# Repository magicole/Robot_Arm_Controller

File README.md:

# Simple Robot Arm Controller
A project for the control of a simple robotic arm with an Arduino. 

This project is based  around control of a MeArm robotic arm with an Arduino Uno. 
It is separated into two main components, hardware and software. 

## Hardware Overview
This project includes an Arduino shield that is capable of controlling 
all 4 degrees of freedom the MeArm has. It also has the capability
to read potentiometer values for use with a "training" mode. Input 
buttons, status LEDs, and a voltage regulator circuit will also be
placed on the board.

## Software Overview
The software for this project is designed either to run standalone
on the arduino or in conjunction with companion software on a PC.
Software features include a training mode, inverse kinematics, and
serial control. Training mode utilizes a model of the arm with 
potentiometers in place of servo's. This model is manipulated and the arm
mirrors the motions.

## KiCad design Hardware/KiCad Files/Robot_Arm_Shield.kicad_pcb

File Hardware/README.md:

#Hardware

##KiCad Libraries
I used the freetronics KiCad libraries in order to give me a good schematic
symbol and footprint for the Arduino shield. Their GitHub repo can be found here:
https://github.com/freetronics/freetronics_kicad_library
I followed the easy way to install them and the library files are found in the
resources folder of this directory.

## Power Regulator: 
http://www.digikey.com/product-detail/en/stmicroelectronics/L7805CDT-TR/497-7255-1-ND/1884014

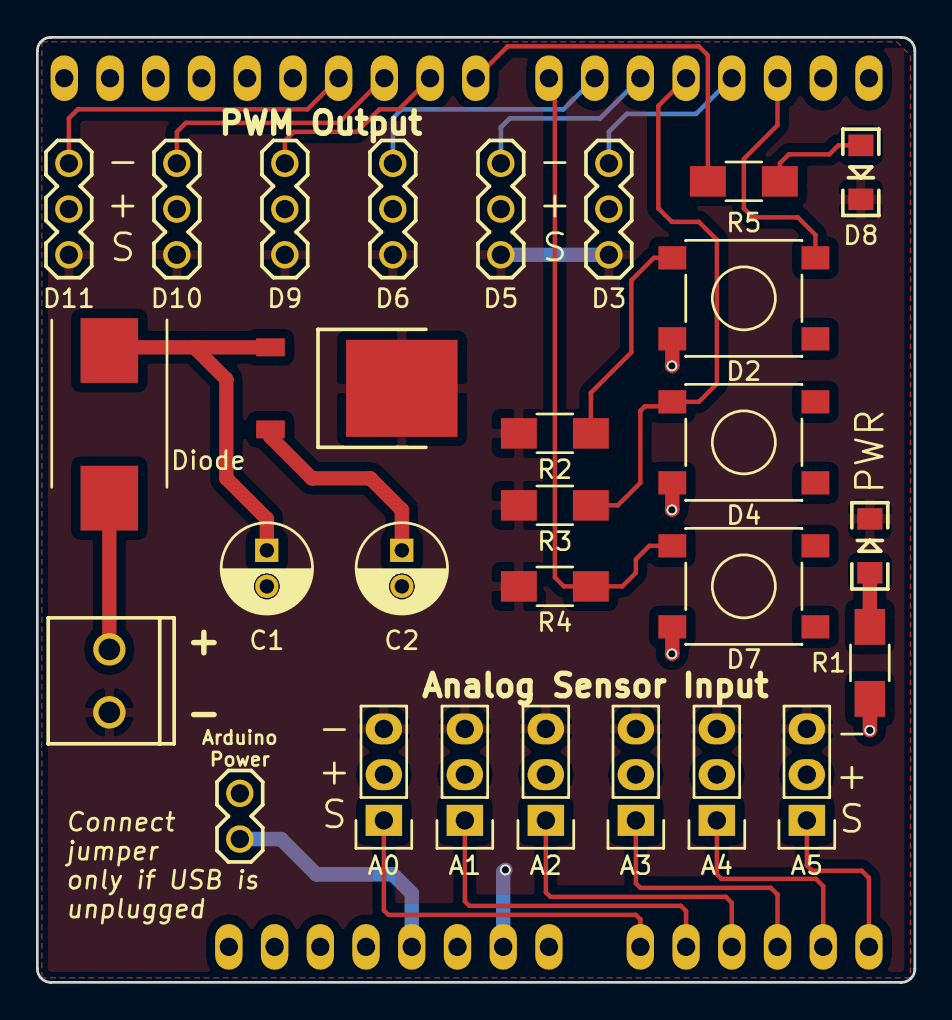
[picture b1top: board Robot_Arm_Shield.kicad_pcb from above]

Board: 2 copper layers, 48.8 x 52.5 mm, 29 parts (0 on the bottom side), 23 nets.

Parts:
A0: Analog In 0; Socket_Strip_Straight_1x03
A1: Analog In 1; Socket_Strip_Straight_1x03
A2: Analog In 2; Socket_Strip_Straight_1x03
A3: Analog In 3; Socket_Strip_Straight_1x03
A4: Analog In 4; Socket_Strip_Straight_1x03
A5: Analog In 5; Socket_Strip_Straight_1x03
C1: 0.33 uF; C_Radial_D5_L11_P2
C2: 0.1 uF; C_Radial_D5_L11_P2
D2: Button 0; SW_SPST_PTS645
D3: Motor 0; 1X03
D4: Button 1; SW_SPST_PTS645
D5: Motor 1; 1X03
D6: Motor 2; 1X03
D7: Button 2; SW_SPST_PTS645
D9: Motor 3; 1X03
D10: Motor 4; 1X03
D11: Motor 5; 1X03
Diode: D_Schottky; DO-214AB_Handsoldering
LED1: Power LED; LED-1206
LED2: Status LED; LED-1206
P1: Power Input; SCREWTERMINAL-3.5MM-2
P14: Power Jumper; 1X02
R1, R5: 150; R_1206_HandSoldering
R2, R3, R4: 10k; R_1206_HandSoldering
SHIELD1: ARDUINO_SHIELD
U1: LM 7805; DPAK

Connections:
/5V: A0.2, A1.2, A2.2, A3.2, A4.2, A5.2, C2.1, D2.1, D3.2, D4.1, D5.2, D6.2, D7.1, D9.2, D10.2, D11.2, P14.1, R1.1, U1.3
/A0: A0.1, SHIELD1.AD0
/A1: A1.1, SHIELD1.AD1
/A2: A2.1, SHIELD1.AD2
/A3: A3.1, SHIELD1.AD3
/A4: A4.1, SHIELD1.AD4
/A5: A5.1, SHIELD1.AD5
/LED0: R5.2, SHIELD1.8
/PWM0: D3.1, SHIELD1.3
/PWM1: D5.1, SHIELD1.5
/PWM2: D6.1, SHIELD1.6
/PWM3: D9.1, SHIELD1.9
/PWM4: D10.1, SHIELD1.10
/PWM5: D11.1, SHIELD1.11
/SW0: D2.2, R2.2, SHIELD1.2
/SW1: D4.2, R3.2, SHIELD1.4
/SW2: D7.2, R4.2, SHIELD1.7
GND: A0.3, A1.3, A2.3, A3.3, A4.3, A5.3, C1.2, C2.2, D3.3, D5.3, D6.3, D9.3, D10.3, D11.3, LED1.K, LED2.K, P1.1, R2.1, R3.1, R4.1, SHIELD1.GND2, U1.2
unnamed: C1.1, Diode.1, U1.1
unnamed: Diode.2, P1.2
unnamed: LED1.A, R1.2
unnamed: LED2.A, R5.1
unnamed: P14.2, SHIELD1.5V

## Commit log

2016-10-10 Update README.md
    Added general project scope and outline
2016-10-12 Initial Hardware Schematic:
    Added schematic for hardware components and exported netlist for pcb layout
2016-10-13 PCB Layout
    Placed parts on board and updated some labels. Also added Freetronics files directly into folder. Edited 7805 symbol to allow for easy footprint placement.
2016-10-15 Finalized Board. Exported Gerbers
